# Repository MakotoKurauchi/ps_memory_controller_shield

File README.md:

# ps memory & controller shield
Arduino shield for reading and writing to Playstation Memorycard

# Parts list
- Memory card connector. (Things taken out from multi-tap)
- Pro Micro
- Diode
- Pin socket
- Pin header
- Jumper pin

# How to assemble

Parts soldering to PCB.
(If use only memory card then need diode and pinsockets. Pin header is no use.)

PCB solerring to Memory card connector.

It is completed by setting pro micro and jumper pins.

# How to use

- [This](https://github.com/MakotoKurauchi/memcarduino/tree/promicro) sketch flash to Pro Micro.
  - https://github.com/MakotoKurauchi/memcarduino/tree/promicro

- Use [this](https://github.com/MakotoKurauchi/memcardrex/tree/promicro) desktop applicaton. Binary is [here](http://yushakobo.jp/blog/wp-content/uploads/2017/09/MemcardRex.zip).
  - https://github.com/MakotoKurauchi/memcardrex/tree/promicro
  - http://yushakobo.jp/blog/wp-content/uploads/2017/09/MemcardRex.zip

# Reference
- [Schematic](https://github.com/MakotoKurauchi/ps_memory_controller_shield/blob/master/pcb/ps_memory_controller_shield.pdf)

# Thanks to:
- [ShendoXT](https://github.com/ShendoXT) - MemCARDuino and MemcardRex creator.

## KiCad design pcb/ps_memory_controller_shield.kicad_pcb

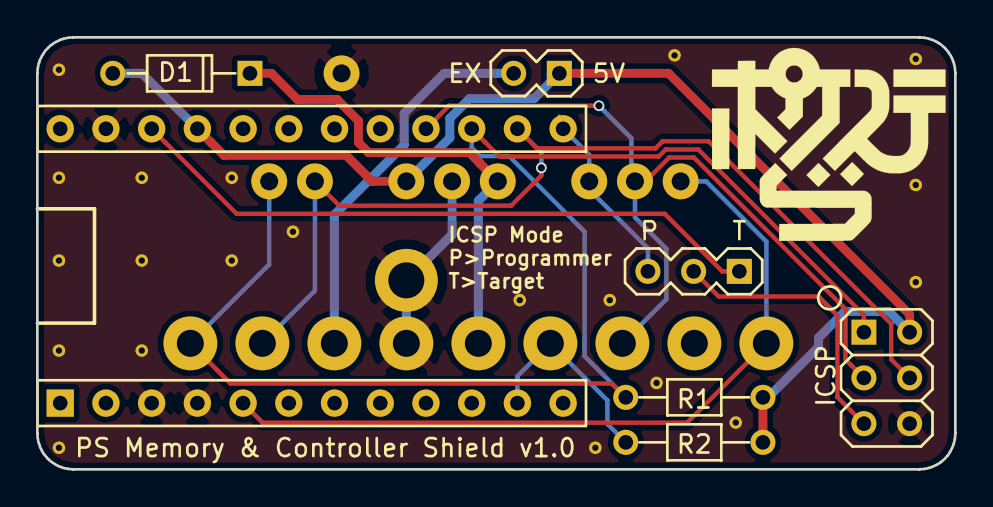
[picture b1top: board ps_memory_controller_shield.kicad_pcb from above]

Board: 2 copper layers, 51.0 x 24.0 mm, 9 parts (1 on the bottom side), 12 nets.

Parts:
D1: D; D3
P1: CONN_01X02; MY_SIL-2
P2: CONN_01X03; MY_SIL-3
P3: ICSP; MY_SIL-2x3
P4: memory&controller; ps_memory_controller
R1, R2: 1k; R3
U1: ProMicro
VAL: LOGO_YUSHAKOBO_B_10mm

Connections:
+3V3: D1.1, P4.5, P4.13
+5V: D1.2, P1.1, P3.2, P4.3, R1.2, R2.2, U1.21
+9V: P1.2, P4.11
/~RESET: P2.1, U1.22
GND: P3.6, P4.4, P4.12, U1.3, U1.4, U1.23
unnamed: P2.2, P3.5
acknowledge: P4.8, P4.17, U1.5
attention: P2.3, P4.6, U1.13
c_attention: P4.14, R2.1, U1.11
clock: P3.3, P4.7, P4.15, U1.16
command: P3.4, P4.2, P4.10, U1.14
data: P3.1, P4.1, P4.9, R1.1, U1.15

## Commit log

2017-09-04 First commit.
2017-09-04 link fix.
2018-08-08 fix link
